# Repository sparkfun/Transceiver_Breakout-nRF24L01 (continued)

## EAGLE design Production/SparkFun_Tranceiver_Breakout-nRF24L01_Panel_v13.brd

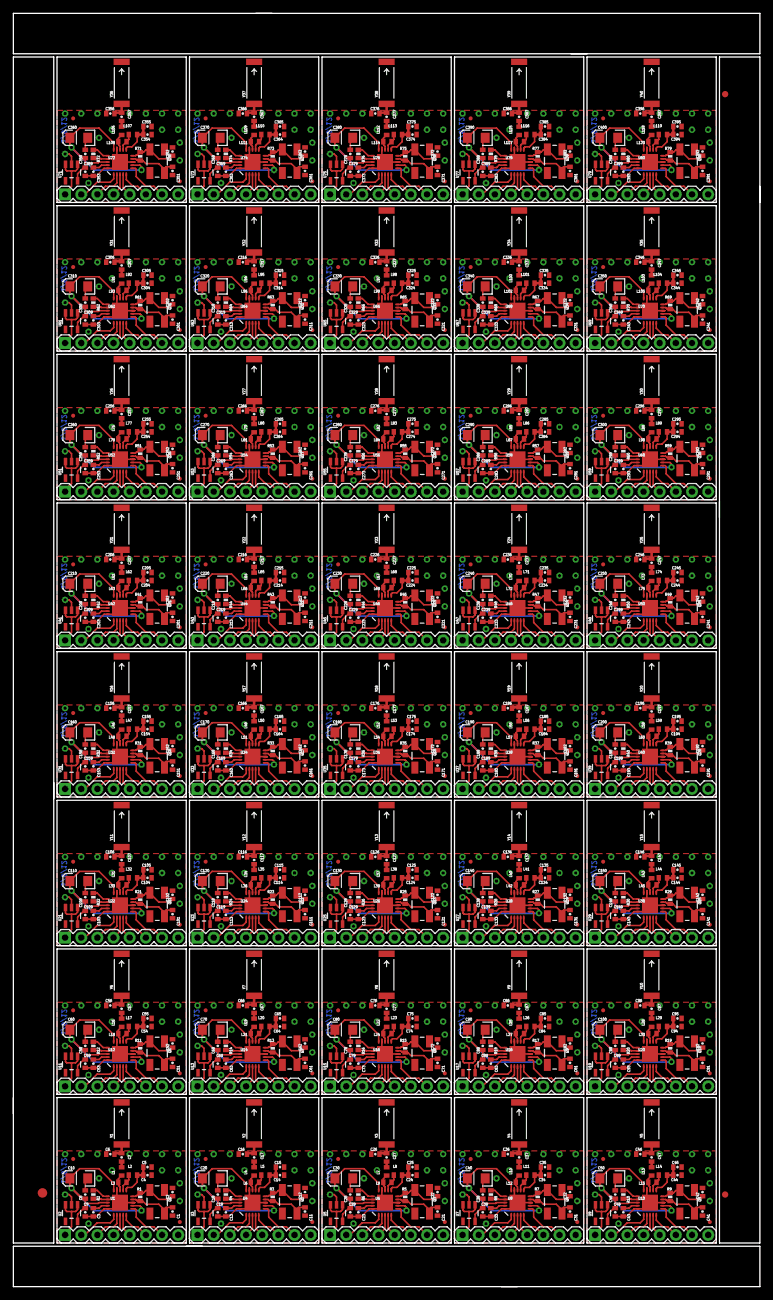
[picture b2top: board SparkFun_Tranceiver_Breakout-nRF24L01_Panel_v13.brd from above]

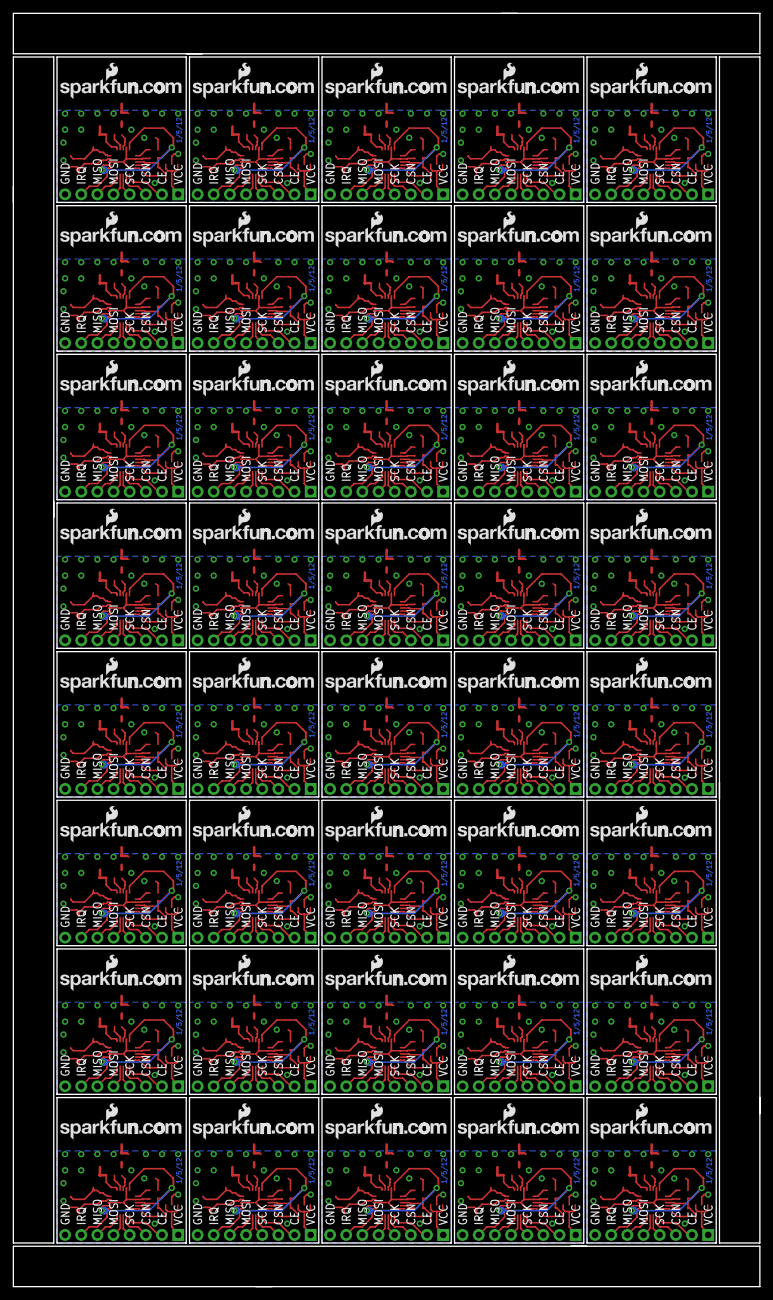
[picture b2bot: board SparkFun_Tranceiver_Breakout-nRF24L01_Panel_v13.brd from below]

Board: 2 copper layers, 117.3 x 200.2 mm, 1043 parts (80 on the bottom side), 720 nets.

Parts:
C1, C2, C11, C12, C21, C22, C31, C32, C41, C42, C51, C52, C61, C62, C71, C72, C81, C82, C91, C92, C101, C102, C111, C112, C121, C122, C131, C132, C141, C142, C151, C152, C161, C162, C171, C172, C181, C182, C191, C192, C201, C202, C211, C212, C221, C222, C231, C232, C241, C242, C251, C252, C261, C262, C271, C272, C281, C282, C291, C292, C301, C302, C311, C312, C321, C322, C331, C332, C341, C342, C351, C352, C361, C362, C371, C372, C381, C382, C391, C392: 22pF; 0402-CAP
C3, C13, C23, C33, C43, C53, C63, C73, C83, C93, C103, C113, C123, C133, C143, C153, C163, C173, C183, C193, C203, C213, C223, C233, C243, C253, C263, C273, C283, C293, C303, C313, C323, C333, C343, C353, C363, C373, C383, C393: 33nF; 0402-CAP
C4, C14, C24, C34, C44, C54, C64, C74, C84, C94, C104, C114, C124, C134, C144, C154, C164, C174, C184, C194, C204, C214, C224, C234, C244, C254, C264, C274, C284, C294, C304, C314, C324, C334, C344, C354, C364, C374, C384, C394: 2.2nF; 0402-CAP
C5, C15, C25, C35, C45, C55, C65, C75, C85, C95, C105, C115, C125, C135, C145, C155, C165, C175, C185, C195, C205, C215, C225, C235, C245, C255, C265, C275, C285, C295, C305, C315, C325, C335, C345, C355, C365, C375, C385, C395: 4.7pF; 0402-CAP
C6, C16, C26, C36, C46, C56, C66, C76, C86, C96, C106, C116, C126, C136, C146, C156, C166, C176, C186, C196, C206, C216, C226, C236, C246, C256, C266, C276, C286, C296, C306, C316, C326, C336, C346, C356, C366, C376, C386, C396: 1.0pF; 0402-CAP
C7, C17, C27, C37, C47, C57, C67, C77, C87, C97, C107, C117, C127, C137, C147, C157, C167, C177, C187, C197, C207, C217, C227, C237, C247, C257, C267, C277, C287, C297, C307, C317, C327, C337, C347, C357, C367, C377, C387, C397: 1.5pF; 0402-CAP
C8, C18, C28, C38, C48, C58, C68, C78, C88, C98, C108, C118, C128, C138, C148, C158, C168, C178, C188, C198, C208, C218, C228, C238, C248, C258, C268, C278, C288, C298, C308, C318, C328, C338, C348, C358, C368, C378, C388, C398: 10nF; 0402-CAP
C9, C19, C29, C39, C49, C59, C69, C79, C89, C99, C109, C119, C129, C139, C149, C159, C169, C179, C189, C199, C209, C219, C229, C239, C249, C259, C269, C279, C289, C299, C309, C319, C329, C339, C349, C359, C369, C379, C389, C399: 1nF; 0402-CAP
C10, C20, C30, C40, C50, C60, C70, C80, C90, C100, C110, C120, C130, C140, C150, C160, C170, C180, C190, C200, C210, C220, C230, C240, C250, C260, C270, C280, C290, C300, C310, C320, C330, C340, C350, C360, C370, C380, C390, C400: 10uF; EIA3216
E$1: FIDUCIAL-1.5X3
E$7, E$8: FIDUCIAL-1X2
JP1, JP4, JP7, JP10, JP13, JP16, JP19, JP22, JP25, JP28, JP31, JP34, JP37, JP40, JP43, JP46, JP49, JP52, JP55, JP58, JP61, JP64, JP67, JP70, JP73, JP76, JP79, JP82, JP85, JP88, JP91, JP94, JP97, JP100, JP103, JP106, JP109, JP112, JP115, JP118: 1X08
JP2, JP3, JP5, JP6, JP8, JP9, JP11, JP12, JP14, JP15, JP17, JP18, JP20, JP21, JP23, JP24, JP26, JP27, JP29, JP30, JP32, JP33, JP35, JP36, JP38, JP39, JP41, JP42, JP44, JP45, JP47, JP48, JP50, JP51, JP53, JP54, JP56, JP57, JP59, JP60, JP62, JP63, JP65, JP66, JP68, JP69, JP71, JP72, JP74, JP75, JP77, JP78, JP80, JP81, JP83, JP84, JP86, JP87, JP89, JP90, JP92, JP93, JP95, JP96, JP98, JP99, JP101, JP102, JP104, JP105, JP107, JP108, JP110, JP111, JP113, JP114, JP116, JP117, JP119, JP120: FIDUCIALUFIDUCIAL; MICRO-FIDUCIAL
L1, L4, L7, L10, L13, L16, L19, L22, L25, L28, L31, L34, L37, L40, L43, L46, L49, L52, L55, L58, L61, L64, L67, L70, L73, L76, L79, L82, L85, L88, L91, L94, L97, L100, L103, L106, L109, L112, L115, L118: 3.9nH; C0402
L2, L5, L8, L11, L14, L17, L20, L23, L26, L29, L32, L35, L38, L41, L44, L47, L50, L53, L56, L59, L62, L65, L68, L71, L74, L77, L80, L83, L86, L89, L92, L95, L98, L101, L104, L107, L110, L113, L116, L119: 2.7nH; C0402
L3, L6, L9, L12, L15, L18, L21, L24, L27, L30, L33, L36, L39, L42, L45, L48, L51, L54, L57, L60, L63, L66, L69, L72, L75, L78, L81, L84, L87, L90, L93, L96, L99, L102, L105, L108, L111, L114, L117, L120: 8.2nH; C0402
Q1, Q2, Q3, Q4, Q5, Q6, Q7, Q8, Q9, Q10, Q11, Q12, Q13, Q14, Q15, Q16, Q17, Q18, Q19, Q20, Q21, Q22, Q23, Q24, Q25, Q26, Q27, Q28, Q29, Q30, Q31, Q32, Q33, Q34, Q35, Q36, Q37, Q38, Q39, Q40: 16MHz; CRYSTAL-SMD-5X3
R1, R3, R5, R7, R9, R11, R13, R15, R17, R19, R21, R23, R25, R27, R29, R31, R33, R35, R37, R39, R41, R43, R45, R47, R49, R51, R53, R55, R57, R59, R61, R63, R65, R67, R69, R71, R73, R75, R77, R79: 1M; 0402-RES
R2, R4, R6, R8, R10, R12, R14, R16, R18, R20, R22, R24, R26, R28, R30, R32, R34, R36, R38, R40, R42, R44, R46, R48, R50, R52, R54, R56, R58, R60, R62, R64, R66, R68, R70, R72, R74, R76, R78, R80: 22K; 0402-RES
TP1, TP2, TP3, TP4, TP5, TP6, TP7, TP8, TP9, TP10, TP11, TP12, TP13, TP14, TP15, TP16, TP17, TP18, TP19, TP20, TP21, TP22, TP23, TP24, TP25, TP26, TP27, TP28, TP29, TP30, TP31, TP32, TP33, TP34, TP35, TP36, TP37, TP38, TP39, TP40: PAD.03X.05
U1, U4, U6, U8, U10, U12, U14, U16, U18, U20, U22, U24, U26, U28, U30, U32, U34, U36, U38, U40, U42, U44, U46, U48, U50, U52, U54, U56, U58, U60, U62, U64, U66, U68, U70, U72, U74, U76, U78, U80: NRF24L01ALT1; QFN20_ALT1
U2, U3, U5, U7, U9, U11, U13, U15, U17, U19, U21, U23, U25, U27, U29, U31, U33, U35, U37, U39, U41, U43, U45, U47, U49, U51, U53, U55, U57, U59, U61, U63, U65, U67, U69, U71, U73, U75, U77, U79: 3.3V; SOT23-5
U$1, U$3, U$4, U$6, U$8, U$9, U$11, U$12, U$14, U$15, U$17, U$18, U$20, U$21, U$23, U$24, U$26, U$27, U$29, U$30, U$32, U$33, U$35, U$36, U$38, U$39, U$41, U$42, U$44, U$45, U$47, U$48, U$50, U$51, U$53, U$54, U$56, U$57, U$59, U$60, U$62, U$63, U$65, U$66, U$68, U$69, U$71, U$72, U$74, U$75, U$77, U$78, U$80, U$81, U$83, U$84, U$86, U$87, U$89, U$90, U$92, U$93, U$95, U$96, U$98, U$99, U$101, U$102, U$104, U$105, U$107, U$108, U$110, U$111, U$113, U$114, U$116, U$117, U$119, U$120: PAD; PAD-0.008
U$2, U$5, U$7, U$10, U$13, U$16, U$19, U$22, U$25, U$28, U$31, U$34, U$37, U$40, U$43, U$46, U$49, U$52, U$55, U$58, U$61, U$64, U$67, U$70, U$73, U$76, U$79, U$82, U$85, U$88, U$91, U$94, U$97, U$100, U$103, U$106, U$109, U$112, U$115, U$118: LOGO-SFENEW; SFE-NEW-WEBLOGO
Y1, Y2, Y3, Y4, Y5, Y6, Y7, Y8, Y9, Y10, Y11, Y12, Y13, Y14, Y15, Y16, Y17, Y18, Y19, Y20, Y21, Y22, Y23, Y24, Y25, Y26, Y27, Y28, Y29, Y30, Y31, Y32, Y33, Y34, Y35, Y36, Y37, Y38, Y39, Y40: ANTENNA2SMD5; ANTENNA-CHIP5

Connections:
ANT: C6.2, C7.2, Y1.FEED
ANT1: C16.2, C17.2, Y2.FEED
ANT2: C26.2, C27.2, Y3.FEED
ANT3: C36.2, C37.2, Y4.FEED
ANT4: C46.2, C47.2, Y5.FEED
ANT5: C56.2, C57.2, Y6.FEED
ANT6: C66.2, C67.2, Y7.FEED
ANT7: C76.2, C77.2, Y8.FEED
ANT8: C86.2, C87.2, Y9.FEED
ANT9: C96.2, C97.2, Y10.FEED
ANT10: C106.2, C107.2, Y11.FEED
ANT11: C116.2, C117.2, Y12.FEED
ANT12: C126.2, C127.2, Y13.FEED
ANT13: C136.2, C137.2, Y14.FEED
ANT14: C146.2, C147.2, Y15.FEED
ANT15: C156.2, C157.2, Y16.FEED
ANT16: C166.2, C167.2, Y17.FEED
ANT17: C176.2, C177.2, Y18.FEED
ANT18: C186.2, C187.2, Y19.FEED
ANT19: C196.2, C197.2, Y20.FEED
ANT20: C206.2, C207.2, Y21.FEED
ANT21: C216.2, C217.2, Y22.FEED
ANT22: C226.2, C227.2, Y23.FEED
ANT23: C236.2, C237.2, Y24.FEED
ANT24: C246.2, C247.2, Y25.FEED
ANT25: C256.2, C257.2, Y26.FEED
ANT26: C266.2, C267.2, Y27.FEED
ANT27: C276.2, C277.2, Y28.FEED
ANT28: C286.2, C287.2, Y29.FEED
ANT29: C296.2, C297.2, Y30.FEED
ANT30: C306.2, C307.2, Y31.FEED
ANT31: C316.2, C317.2, Y32.FEED
ANT32: C326.2, C327.2, Y33.FEED
ANT33: C336.2, C337.2, Y34.FEED
ANT34: C346.2, C347.2, Y35.FEED
ANT35: C356.2, C357.2, Y36.FEED
ANT36: C366.2, C367.2, Y37.FEED
ANT37: C376.2, C377.2, Y38.FEED
ANT38: C386.2, C387.2, Y39.FEED
ANT39: C396.2, C397.2, Y40.FEED
CE: JP1.2, U1.1
CE1: JP4.2, U4.1
CE2: JP7.2, U6.1
CE3: JP10.2, U8.1
CE4: JP13.2, U10.1
CE5: JP16.2, U12.1
CE6: JP19.2, U14.1
CE7: JP22.2, U16.1
CE8: JP25.2, U18.1
CE9: JP28.2, U20.1
CE10: JP31.2, U22.1
CE11: JP34.2, U24.1
CE12: JP37.2, U26.1
CE13: JP40.2, U28.1
CE14: JP43.2, U30.1
CE15: JP46.2, U32.1
CE16: JP49.2, U34.1
CE17: JP52.2, U36.1
CE18: JP55.2, U38.1
CE19: JP58.2, U40.1
CE20: JP61.2, U42.1
CE21: JP64.2, U44.1
CE22: JP67.2, U46.1
CE23: JP70.2, U48.1
CE24: JP73.2, U50.1
CE25: JP76.2, U52.1
CE26: JP79.2, U54.1
CE27: JP82.2, U56.1
CE28: JP85.2, U58.1
CE29: JP88.2, U60.1
CE30: JP91.2, U62.1
CE31: JP94.2, U64.1
CE32: JP97.2, U66.1
CE33: JP100.2, U68.1
CE34: JP103.2, U70.1
CE35: JP106.2, U72.1
CE36: JP109.2, U74.1
CE37: JP112.2, U76.1
CE38: JP115.2, U78.1
CE39: JP118.2, U80.1
CSN: JP1.3, U1.2
CSN1: JP4.3, U4.2
CSN2: JP7.3, U6.2
CSN3: JP10.3, U8.2
CSN4: JP13.3, U10.2
CSN5: JP16.3, U12.2
CSN6: JP19.3, U14.2
CSN7: JP22.3, U16.2
CSN8: JP25.3, U18.2
CSN9: JP28.3, U20.2
CSN10: JP31.3, U22.2
CSN11: JP34.3, U24.2
CSN12: JP37.3, U26.2
CSN13: JP40.3, U28.2
CSN14: JP43.3, U30.2
CSN15: JP46.3, U32.2
CSN16: JP49.3, U34.2
CSN17: JP52.3, U36.2
CSN18: JP55.3, U38.2
CSN19: JP58.3, U40.2
CSN20: JP61.3, U42.2
CSN21: JP64.3, U44.2
CSN22: JP67.3, U46.2
CSN23: JP70.3, U48.2
CSN24: JP73.3, U50.2
CSN25: JP76.3, U52.2
CSN26: JP79.3, U54.2
CSN27: JP82.3, U56.2
CSN28: JP85.3, U58.2
CSN29: JP88.3, U60.2
CSN30: JP91.3, U62.2
CSN31: JP94.3, U64.2
CSN32: JP97.3, U66.2
CSN33: JP100.3, U68.2
CSN34: JP103.3, U70.2
CSN35: JP106.3, U72.2
CSN36: JP109.3, U74.2
CSN37: JP112.3, U76.2
CSN38: JP115.3, U78.2
CSN39: JP118.3, U80.2
GND: C1.2, C2.2, C3.2, C4.2, C5.2, C6.1, C8.1, C9.1, C10.C, JP1.8, R2.2, U1.0, U1.8, U1.14, U1.17, U1.20, U2.2, U$1.P$1, U$4.P$1
GND1: C11.2, C12.2, C13.2, C14.2, C15.2, C16.1, C18.1, C19.1, C20.C, JP4.8, R4.2, U3.2, U4.0, U4.8, U4.14, U4.17, U4.20, U$3.P$1, U$6.P$1
GND2: C21.2, C22.2, C23.2, C24.2, C25.2, C26.1, C28.1, C29.1, C30.C, JP7.8, R6.2, U5.2, U6.0, U6.8, U6.14, U6.17, U6.20, U$8.P$1, U$9.P$1
GND3: C31.2, C32.2, C33.2, C34.2, C35.2, C36.1, C38.1, C39.1, C40.C, JP10.8, R8.2, U7.2, U8.0, U8.8, U8.14, U8.17, U8.20, U$11.P$1, U$12.P$1
GND4: C41.2, C42.2, C43.2, C44.2, C45.2, C46.1, C48.1, C49.1, C50.C, JP13.8, R10.2, U9.2, U10.0, U10.8, U10.14, U10.17, U10.20, U$14.P$1, U$15.P$1
GND5: C51.2, C52.2, C53.2, C54.2, C55.2, C56.1, C58.1, C59.1, C60.C, JP16.8, R12.2, U11.2, U12.0, U12.8, U12.14, U12.17, U12.20, U$17.P$1, U$18.P$1
GND6: C61.2, C62.2, C63.2, C64.2, C65.2, C66.1, C68.1, C69.1, C70.C, JP19.8, R14.2, U13.2, U14.0, U14.8, U14.14, U14.17, U14.20, U$20.P$1, U$21.P$1
GND7: C71.2, C72.2, C73.2, C74.2, C75.2, C76.1, C78.1, C79.1, C80.C, JP22.8, R16.2, U15.2, U16.0, U16.8, U16.14, U16.17, U16.20, U$23.P$1, U$24.P$1
GND8: C81.2, C82.2, C83.2, C84.2, C85.2, C86.1, C88.1, C89.1, C90.C, JP25.8, R18.2, U17.2, U18.0, U18.8, U18.14, U18.17, U18.20, U$26.P$1, U$27.P$1
GND9: C91.2, C92.2, C93.2, C94.2, C95.2, C96.1, C98.1, C99.1, C100.C, JP28.8, R20.2, U19.2, U20.0, U20.8, U20.14, U20.17, U20.20, U$29.P$1, U$30.P$1
GND10: C101.2, C102.2, C103.2, C104.2, C105.2, C106.1, C108.1, C109.1, C110.C, JP31.8, R22.2, U21.2, U22.0, U22.8, U22.14, U22.17, U22.20, U$32.P$1, U$33.P$1
GND11: C111.2, C112.2, C113.2, C114.2, C115.2, C116.1, C118.1, C119.1, C120.C, JP34.8, R24.2, U23.2, U24.0, U24.8, U24.14, U24.17, U24.20, U$35.P$1, U$36.P$1
GND12: C121.2, C122.2, C123.2, C124.2, C125.2, C126.1, C128.1, C129.1, C130.C, JP37.8, R26.2, U25.2, U26.0, U26.8, U26.14, U26.17, U26.20, U$38.P$1, U$39.P$1
GND13: C131.2, C132.2, C133.2, C134.2, C135.2, C136.1, C138.1, C139.1, C140.C, JP40.8, R28.2, U27.2, U28.0, U28.8, U28.14, U28.17, U28.20, U$41.P$1, U$42.P$1
GND14: C141.2, C142.2, C143.2, C144.2, C145.2, C146.1, C148.1, C149.1, C150.C, JP43.8, R30.2, U29.2, U30.0, U30.8, U30.14, U30.17, U30.20, U$44.P$1, U$45.P$1
GND15: C151.2, C152.2, C153.2, C154.2, C155.2, C156.1, C158.1, C159.1, C160.C, JP46.8, R32.2, U31.2, U32.0, U32.8, U32.14, U32.17, U32.20, U$47.P$1, U$48.P$1
GND16: C161.2, C162.2, C163.2, C164.2, C165.2, C166.1, C168.1, C169.1, C170.C, JP49.8, R34.2, U33.2, U34.0, U34.8, U34.14, U34.17, U34.20, U$50.P$1, U$51.P$1
GND17: C171.2, C172.2, C173.2, C174.2, C175.2, C176.1, C178.1, C179.1, C180.C, JP52.8, R36.2, U35.2, U36.0, U36.8, U36.14, U36.17, U36.20, U$53.P$1, U$54.P$1
GND18: C181.2, C182.2, C183.2, C184.2, C185.2, C186.1, C188.1, C189.1, C190.C, JP55.8, R38.2, U37.2, U38.0, U38.8, U38.14, U38.17, U38.20, U$56.P$1, U$57.P$1
GND19: C191.2, C192.2, C193.2, C194.2, C195.2, C196.1, C198.1, C199.1, C200.C, JP58.8, R40.2, U39.2, U40.0, U40.8, U40.14, U40.17, U40.20, U$59.P$1, U$60.P$1
GND20: C201.2, C202.2, C203.2, C204.2, C205.2, C206.1, C208.1, C209.1, C210.C, JP61.8, R42.2, U41.2, U42.0, U42.8, U42.14, U42.17, U42.20, U$62.P$1, U$63.P$1
GND21: C211.2, C212.2, C213.2, C214.2, C215.2, C216.1, C218.1, C219.1, C220.C, JP64.8, R44.2, U43.2, U44.0, U44.8, U44.14, U44.17, U44.20, U$65.P$1, U$66.P$1
GND22: C221.2, C222.2, C223.2, C224.2, C225.2, C226.1, C228.1, C229.1, C230.C, JP67.8, R46.2, U45.2, U46.0, U46.8, U46.14, U46.17, U46.20, U$68.P$1, U$69.P$1
GND23: C231.2, C232.2, C233.2, C234.2, C235.2, C236.1, C238.1, C239.1, C240.C, JP70.8, R48.2, U47.2, U48.0, U48.8, U48.14, U48.17, U48.20, U$71.P$1, U$72.P$1
GND24: C241.2, C242.2, C243.2, C244.2, C245.2, C246.1, C248.1, C249.1, C250.C, JP73.8, R50.2, U49.2, U50.0, U50.8, U50.14, U50.17, U50.20, U$74.P$1, U$75.P$1
GND25: C251.2, C252.2, C253.2, C254.2, C255.2, C256.1, C258.1, C259.1, C260.C, JP76.8, R52.2, U51.2, U52.0, U52.8, U52.14, U52.17, U52.20, U$77.P$1, U$78.P$1
GND26: C261.2, C262.2, C263.2, C264.2, C265.2, C266.1, C268.1, C269.1, C270.C, JP79.8, R54.2, U53.2, U54.0, U54.8, U54.14, U54.17, U54.20, U$80.P$1, U$81.P$1
GND27: C271.2, C272.2, C273.2, C274.2, C275.2, C276.1, C278.1, C279.1, C280.C, JP82.8, R56.2, U55.2, U56.0, U56.8, U56.14, U56.17, U56.20, U$83.P$1, U$84.P$1
GND28: C281.2, C282.2, C283.2, C284.2, C285.2, C286.1, C288.1, C289.1, C290.C, JP85.8, R58.2, U57.2, U58.0, U58.8, U58.14, U58.17, U58.20, U$86.P$1, U$87.P$1
GND29: C291.2, C292.2, C293.2, C294.2, C295.2, C296.1, C298.1, C299.1, C300.C, JP88.8, R60.2, U59.2, U60.0, U60.8, U60.14, U60.17, U60.20, U$89.P$1, U$90.P$1
GND30: C301.2, C302.2, C303.2, C304.2, C305.2, C306.1, C308.1, C309.1, C310.C, JP91.8, R62.2, U61.2, U62.0, U62.8, U62.14, U62.17, U62.20, U$92.P$1, U$93.P$1
GND31: C311.2, C312.2, C313.2, C314.2, C315.2, C316.1, C318.1, C319.1, C320.C, JP94.8, R64.2, U63.2, U64.0, U64.8, U64.14, U64.17, U64.20, U$95.P$1, U$96.P$1
GND32: C321.2, C322.2, C323.2, C324.2, C325.2, C326.1, C328.1, C329.1, C330.C, JP97.8, R66.2, U65.2, U66.0, U66.8, U66.14, U66.17, U66.20, U$98.P$1, U$99.P$1
GND33: C331.2, C332.2, C333.2, C334.2, C335.2, C336.1, C338.1, C339.1, C340.C, JP100.8, R68.2, U67.2, U68.0, U68.8, U68.14, U68.17, U68.20, U$101.P$1, U$102.P$1
GND34: C341.2, C342.2, C343.2, C344.2, C345.2, C346.1, C348.1, C349.1, C350.C, JP103.8, R70.2, U69.2, U70.0, U70.8, U70.14, U70.17, U70.20, U$104.P$1, U$105.P$1
GND35: C351.2, C352.2, C353.2, C354.2, C355.2, C356.1, C358.1, C359.1, C360.C, JP106.8, R72.2, U71.2, U72.0, U72.8, U72.14, U72.17, U72.20, U$107.P$1, U$108.P$1
GND36: C361.2, C362.2, C363.2, C364.2, C365.2, C366.1, C368.1, C369.1, C370.C, JP109.8, R74.2, U73.2, U74.0, U74.8, U74.14, U74.17, U74.20, U$110.P$1, U$111.P$1
GND37: C371.2, C372.2, C373.2, C374.2, C375.2, C376.1, C378.1, C379.1, C380.C, JP112.8, R76.2, U75.2, U76.0, U76.8, U76.14, U76.17, U76.20, U$113.P$1, U$114.P$1
GND38: C381.2, C382.2, C383.2, C384.2, C385.2, C386.1, C388.1, C389.1, C390.C, JP115.8, R78.2, U77.2, U78.0, U78.8, U78.14, U78.17, U78.20, U$116.P$1, U$117.P$1
GND39: C391.2, C392.2, C393.2, C394.2, C395.2, C396.1, C398.1, C399.1, C400.C, JP118.8, R80.2, U79.2, U80.0, U80.8, U80.14, U80.17, U80.20, U$119.P$1, U$120.P$1
IQR: JP1.7, U1.6
IQR1: JP4.7, U4.6
IQR2: JP7.7, U6.6
IQR3: JP10.7, U8.6
IQR4: JP13.7, U10.6
IQR5: JP16.7, U12.6
IQR6: JP19.7, U14.6
IQR7: JP22.7, U16.6
IQR8: JP25.7, U18.6
IQR9: JP28.7, U20.6
IQR10: JP31.7, U22.6
IQR11: JP34.7, U24.6
IQR12: JP37.7, U26.6
IQR13: JP40.7, U28.6
IQR14: JP43.7, U30.6
IQR15: JP46.7, U32.6
IQR16: JP49.7, U34.6
IQR17: JP52.7, U36.6
IQR18: JP55.7, U38.6
IQR19: JP58.7, U40.6
IQR20: JP61.7, U42.6
IQR21: JP64.7, U44.6
IQR22: JP67.7, U46.6
IQR23: JP70.7, U48.6
IQR24: JP73.7, U50.6
IQR25: JP76.7, U52.6
IQR26: JP79.7, U54.6
IQR27: JP82.7, U56.6
IQR28: JP85.7, U58.6
IQR29: JP88.7, U60.6
IQR30: JP91.7, U62.6
IQR31: JP94.7, U64.6
IQR32: JP97.7, U66.6
IQR33: JP100.7, U68.6
IQR34: JP103.7, U70.6
IQR35: JP106.7, U72.6
IQR36: JP109.7, U74.6
IQR37: JP112.7, U76.6
IQR38: JP115.7, U78.6
IQR39: JP118.7, U80.6
MISO: JP1.6, U1.5
MISO1: JP4.6, U4.5
MISO2: JP7.6, U6.5
MISO3: JP10.6, U8.5
MISO4: JP13.6, U10.5
MISO5: JP16.6, U12.5
MISO6: JP19.6, U14.5
MISO7: JP22.6, U16.5
MISO8: JP25.6, U18.5
MISO9: JP28.6, U20.5
MISO10: JP31.6, U22.5
MISO11: JP34.6, U24.5
MISO12: JP37.6, U26.5
MISO13: JP40.6, U28.5
MISO14: JP43.6, U30.5
MISO15: JP46.6, U32.5
MISO16: JP49.6, U34.5
MISO17: JP52.6, U36.5
MISO18: JP55.6, U38.5
MISO19: JP58.6, U40.5
MISO20: JP61.6, U42.5
MISO21: JP64.6, U44.5
MISO22: JP67.6, U46.5
MISO23: JP70.6, U48.5
MISO24: JP73.6, U50.5
MISO25: JP76.6, U52.5
MISO26: JP79.6, U54.5
MISO27: JP82.6, U56.5
MISO28: JP85.6, U58.5
MISO29: JP88.6, U60.5
MISO30: JP91.6, U62.5
MISO31: JP94.6, U64.5
MISO32: JP97.6, U66.5
MISO33: JP100.6, U68.5
MISO34: JP103.6, U70.5
MISO35: JP106.6, U72.5
MISO36: JP109.6, U74.5
MISO37: JP112.6, U76.5
MISO38: JP115.6, U78.5
MISO39: JP118.6, U80.5
MOSI: JP1.5, U1.4
MOSI1: JP4.5, U4.4
MOSI2: JP7.5, U6.4
MOSI3: JP10.5, U8.4
MOSI4: JP13.5, U10.4
MOSI5: JP16.5, U12.4
MOSI6: JP19.5, U14.4
MOSI7: JP22.5, U16.4
MOSI8: JP25.5, U18.4
MOSI9: JP28.5, U20.4
MOSI10: JP31.5, U22.4
MOSI11: JP34.5, U24.4
MOSI12: JP37.5, U26.4
MOSI13: JP40.5, U28.4
MOSI14: JP43.5, U30.4
MOSI15: JP46.5, U32.4
MOSI16: JP49.5, U34.4
MOSI17: JP52.5, U36.4
MOSI18: JP55.5, U38.4
MOSI19: JP58.5, U40.4
MOSI20: JP61.5, U42.4
MOSI21: JP64.5, U44.4
MOSI22: JP67.5, U46.4
MOSI23: JP70.5, U48.4
MOSI24: JP73.5, U50.4
MOSI25: JP76.5, U52.4
MOSI26: JP79.5, U54.4
MOSI27: JP82.5, U56.4
MOSI28: JP85.5, U58.4
MOSI29: JP88.5, U60.4
MOSI30: JP91.5, U62.4
MOSI31: JP94.5, U64.4
MOSI32: JP97.5, U66.4
MOSI33: JP100.5, U68.4
MOSI34: JP103.5, U70.4
MOSI35: JP106.5, U72.4
MOSI36: JP109.5, U74.4
MOSI37: JP112.5, U76.4
MOSI38: JP115.5, U78.4
MOSI39: JP118.5, U80.4
unnamed: C1.1, Q1.1, R1.1, U1.9
unnamed: C2.1, Q1.3, R1.2, U1.10
unnamed: L2.2, L3.1, U1.12
unnamed: R2.1, U1.16
unnamed: C3.1, U1.19
unnamed: L1.1, L3.2, U1.13
unnamed: C4.1, C5.1, L2.1, U1.11
unnamed: C11.1, Q2.1, R3.1, U4.9
unnamed: C7.1, L1.2
unnamed: C12.1, Q2.3, R3.2, U4.10
unnamed: L4.1, L6.2, U4.13
unnamed: C14.1, C15.1, L5.1, U4.11
unnamed: R4.1, U4.16
unnamed: C13.1, U4.19
unnamed: L5.2, L6.1, U4.12
unnamed: C17.1, L4.2
unnamed: C21.1, Q3.1, R5.1, U6.9
unnamed: C22.1, Q3.3, R5.2, U6.10
unnamed: L7.1, L9.2, U6.13
unnamed: C24.1, C25.1, L8.1, U6.11
unnamed: R6.1, U6.16
unnamed: C23.1, U6.19
unnamed: L8.2, L9.1, U6.12
unnamed: C27.1, L7.2
unnamed: C31.1, Q4.1, R7.1, U8.9
unnamed: C32.1, Q4.3, R7.2, U8.10
unnamed: L10.1, L12.2, U8.13
unnamed: C34.1, C35.1, L11.1, U8.11
unnamed: R8.1, U8.16
unnamed: C33.1, U8.19
unnamed: L11.2, L12.1, U8.12
unnamed: C37.1, L10.2
unnamed: C41.1, Q5.1, R9.1, U10.9
unnamed: C42.1, Q5.3, R9.2, U10.10
unnamed: L13.1, L15.2, U10.13
unnamed: C44.1, C45.1, L14.1, U10.11
unnamed: R10.1, U10.16
unnamed: C43.1, U10.19
unnamed: L14.2, L15.1, U10.12
unnamed: C47.1, L13.2
unnamed: C51.1, Q6.1, R11.1, U12.9
unnamed: C52.1, Q6.3, R11.2, U12.10
unnamed: L16.1, L18.2, U12.13
unnamed: C54.1, C55.1, L17.1, U12.11
unnamed: R12.1, U12.16
unnamed: C53.1, U12.19
unnamed: L17.2, L18.1, U12.12
unnamed: C57.1, L16.2
unnamed: C61.1, Q7.1, R13.1, U14.9
unnamed: C62.1, Q7.3, R13.2, U14.10
unnamed: L19.1, L21.2, U14.13
unnamed: C64.1, C65.1, L20.1, U14.11
unnamed: R14.1, U14.16
unnamed: C63.1, U14.19
unnamed: L20.2, L21.1, U14.12
unnamed: C67.1, L19.2
unnamed: C71.1, Q8.1, R15.1, U16.9
unnamed: C72.1, Q8.3, R15.2, U16.10
unnamed: L22.1, L24.2, U16.13
unnamed: C74.1, C75.1, L23.1, U16.11
unnamed: R16.1, U16.16
unnamed: C73.1, U16.19
unnamed: L23.2, L24.1, U16.12
unnamed: C77.1, L22.2
unnamed: C81.1, Q9.1, R17.1, U18.9
unnamed: C82.1, Q9.3, R17.2, U18.10
unnamed: L25.1, L27.2, U18.13
unnamed: C84.1, C85.1, L26.1, U18.11
unnamed: R18.1, U18.16
unnamed: C83.1, U18.19
unnamed: L26.2, L27.1, U18.12
unnamed: C87.1, L25.2
unnamed: C91.1, Q10.1, R19.1, U20.9
unnamed: C92.1, Q10.3, R19.2, U20.10
unnamed: L28.1, L30.2, U20.13
unnamed: C94.1, C95.1, L29.1, U20.11
unnamed: R20.1, U20.16
unnamed: C93.1, U20.19
unnamed: L29.2, L30.1, U20.12
unnamed: C97.1, L28.2
unnamed: C101.1, Q11.1, R21.1, U22.9
unnamed: C102.1, Q11.3, R21.2, U22.10
unnamed: L31.1, L33.2, U22.13
unnamed: C104.1, C105.1, L32.1, U22.11
unnamed: R22.1, U22.16
unnamed: C103.1, U22.19
unnamed: L32.2, L33.1, U22.12
unnamed: C107.1, L31.2
unnamed: C111.1, Q12.1, R23.1, U24.9
unnamed: C112.1, Q12.3, R23.2, U24.10
unnamed: L34.1, L36.2, U24.13
unnamed: C114.1, C115.1, L35.1, U24.11
unnamed: R24.1, U24.16
unnamed: C113.1, U24.19
unnamed: L35.2, L36.1, U24.12
unnamed: C117.1, L34.2
unnamed: C121.1, Q13.1, R25.1, U26.9
unnamed: C122.1, Q13.3, R25.2, U26.10
unnamed: L37.1, L39.2, U26.13
unnamed: C124.1, C125.1, L38.1, U26.11
unnamed: R26.1, U26.16
unnamed: C123.1, U26.19
unnamed: L38.2, L39.1, U26.12
unnamed: C127.1, L37.2
unnamed: C131.1, Q14.1, R27.1, U28.9
unnamed: C132.1, Q14.3, R27.2, U28.10
unnamed: L40.1, L42.2, U28.13
unnamed: C134.1, C135.1, L41.1, U28.11
unnamed: R28.1, U28.16
unnamed: C133.1, U28.19
unnamed: L41.2, L42.1, U28.12
unnamed: C137.1, L40.2
unnamed: C141.1, Q15.1, R29.1, U30.9
unnamed: C142.1, Q15.3, R29.2, U30.10
unnamed: L43.1, L45.2, U30.13
unnamed: C144.1, C145.1, L44.1, U30.11
unnamed: R30.1, U30.16
unnamed: C143.1, U30.19
unnamed: L44.2, L45.1, U30.12
unnamed: C147.1, L43.2
unnamed: C151.1, Q16.1, R31.1, U32.9
unnamed: C152.1, Q16.3, R31.2, U32.10
unnamed: L46.1, L48.2, U32.13
unnamed: C154.1, C155.1, L47.1, U32.11
unnamed: R32.1, U32.16
unnamed: C153.1, U32.19
unnamed: L47.2, L48.1, U32.12
unnamed: C157.1, L46.2
unnamed: C161.1, Q17.1, R33.1, U34.9
unnamed: C162.1, Q17.3, R33.2, U34.10
unnamed: L49.1, L51.2, U34.13
unnamed: C164.1, C165.1, L50.1, U34.11
unnamed: R34.1, U34.16
unnamed: C163.1, U34.19
unnamed: L50.2, L51.1, U34.12
unnamed: C167.1, L49.2
unnamed: C171.1, Q18.1, R35.1, U36.9
unnamed: C172.1, Q18.3, R35.2, U36.10
unnamed: L52.1, L54.2, U36.13
unnamed: C174.1, C175.1, L53.1, U36.11
unnamed: R36.1, U36.16
unnamed: C173.1, U36.19
unnamed: L53.2, L54.1, U36.12
unnamed: C177.1, L52.2
unnamed: C181.1, Q19.1, R37.1, U38.9
unnamed: C182.1, Q19.3, R37.2, U38.10
unnamed: L55.1, L57.2, U38.13
unnamed: C184.1, C185.1, L56.1, U38.11
unnamed: R38.1, U38.16
unnamed: C183.1, U38.19
unnamed: L56.2, L57.1, U38.12
unnamed: C187.1, L55.2
unnamed: C191.1, Q20.1, R39.1, U40.9
unnamed: C192.1, Q20.3, R39.2, U40.10
unnamed: L58.1, L60.2, U40.13
unnamed: C194.1, C195.1, L59.1, U40.11
unnamed: R40.1, U40.16
unnamed: C193.1, U40.19
unnamed: L59.2, L60.1, U40.12
unnamed: C197.1, L58.2
unnamed: C201.1, Q21.1, R41.1, U42.9
unnamed: C202.1, Q21.3, R41.2, U42.10
unnamed: L61.1, L63.2, U42.13
unnamed: C204.1, C205.1, L62.1, U42.11
unnamed: R42.1, U42.16
unnamed: C203.1, U42.19
unnamed: L62.2, L63.1, U42.12
unnamed: C207.1, L61.2
unnamed: C211.1, Q22.1, R43.1, U44.9
unnamed: C212.1, Q22.3, R43.2, U44.10
unnamed: L64.1, L66.2, U44.13
unnamed: C214.1, C215.1, L65.1, U44.11
unnamed: R44.1, U44.16
unnamed: C213.1, U44.19
unnamed: L65.2, L66.1, U44.12
unnamed: C217.1, L64.2
unnamed: C221.1, Q23.1, R45.1, U46.9
unnamed: C222.1, Q23.3, R45.2, U46.10
unnamed: L67.1, L69.2, U46.13
unnamed: C224.1, C225.1, L68.1, U46.11
unnamed: R46.1, U46.16
unnamed: C223.1, U46.19
unnamed: L68.2, L69.1, U46.12
unnamed: C227.1, L67.2
unnamed: C231.1, Q24.1, R47.1, U48.9
unnamed: C232.1, Q24.3, R47.2, U48.10
unnamed: L70.1, L72.2, U48.13
unnamed: C234.1, C235.1, L71.1, U48.11
unnamed: R48.1, U48.16
unnamed: C233.1, U48.19
unnamed: L71.2, L72.1, U48.12
unnamed: C237.1, L70.2
unnamed: C241.1, Q25.1, R49.1, U50.9
unnamed: C242.1, Q25.3, R49.2, U50.10
unnamed: L73.1, L75.2, U50.13
unnamed: C244.1, C245.1, L74.1, U50.11
unnamed: R50.1, U50.16
unnamed: C243.1, U50.19
unnamed: L74.2, L75.1, U50.12
unnamed: C247.1, L73.2
unnamed: C251.1, Q26.1, R51.1, U52.9
unnamed: C252.1, Q26.3, R51.2, U52.10
unnamed: L76.1, L78.2, U52.13
unnamed: C254.1, C255.1, L77.1, U52.11
unnamed: R52.1, U52.16
unnamed: C253.1, U52.19
unnamed: L77.2, L78.1, U52.12
unnamed: C257.1, L76.2
unnamed: C261.1, Q27.1, R53.1, U54.9
unnamed: C262.1, Q27.3, R53.2, U54.10
unnamed: L79.1, L81.2, U54.13
unnamed: C264.1, C265.1, L80.1, U54.11
unnamed: R54.1, U54.16
unnamed: C263.1, U54.19
unnamed: L80.2, L81.1, U54.12
unnamed: C267.1, L79.2
unnamed: C271.1, Q28.1, R55.1, U56.9
unnamed: C272.1, Q28.3, R55.2, U56.10
unnamed: L82.1, L84.2, U56.13
unnamed: C274.1, C275.1, L83.1, U56.11
unnamed: R56.1, U56.16
unnamed: C273.1, U56.19
unnamed: L83.2, L84.1, U56.12
unnamed: C277.1, L82.2
unnamed: C281.1, Q29.1, R57.1, U58.9
unnamed: C282.1, Q29.3, R57.2, U58.10
unnamed: L85.1, L87.2, U58.13
unnamed: C284.1, C285.1, L86.1, U58.11
unnamed: R58.1, U58.16
unnamed: C283.1, U58.19
unnamed: L86.2, L87.1, U58.12
unnamed: C287.1, L85.2
unnamed: C291.1, Q30.1, R59.1, U60.9
unnamed: C292.1, Q30.3, R59.2, U60.10
unnamed: L88.1, L90.2, U60.13
unnamed: C294.1, C295.1, L89.1, U60.11
unnamed: R60.1, U60.16
unnamed: C293.1, U60.19
unnamed: L89.2, L90.1, U60.12
unnamed: C297.1, L88.2
unnamed: C301.1, Q31.1, R61.1, U62.9
unnamed: C302.1, Q31.3, R61.2, U62.10
unnamed: L91.1, L93.2, U62.13
unnamed: C304.1, C305.1, L92.1, U62.11
unnamed: R62.1, U62.16
unnamed: C303.1, U62.19
unnamed: L92.2, L93.1, U62.12
unnamed: C307.1, L91.2
unnamed: C311.1, Q32.1, R63.1, U64.9
unnamed: C312.1, Q32.3, R63.2, U64.10
unnamed: L94.1, L96.2, U64.13
unnamed: C314.1, C315.1, L95.1, U64.11
unnamed: R64.1, U64.16
unnamed: C313.1, U64.19
unnamed: L95.2, L96.1, U64.12
unnamed: C317.1, L94.2
unnamed: C321.1, Q33.1, R65.1, U66.9
unnamed: C322.1, Q33.3, R65.2, U66.10
unnamed: L97.1, L99.2, U66.13
unnamed: C324.1, C325.1, L98.1, U66.11
unnamed: R66.1, U66.16
unnamed: C323.1, U66.19
unnamed: L98.2, L99.1, U66.12
unnamed: C327.1, L97.2
unnamed: C331.1, Q34.1, R67.1, U68.9
unnamed: C332.1, Q34.3, R67.2, U68.10
unnamed: L100.1, L102.2, U68.13
unnamed: C334.1, C335.1, L101.1, U68.11
unnamed: R68.1, U68.16
unnamed: C333.1, U68.19
unnamed: L101.2, L102.1, U68.12
unnamed: C337.1, L100.2
unnamed: C341.1, Q35.1, R69.1, U70.9
unnamed: C342.1, Q35.3, R69.2, U70.10
unnamed: L103.1, L105.2, U70.13
unnamed: C344.1, C345.1, L104.1, U70.11
unnamed: R70.1, U70.16
unnamed: C343.1, U70.19
unnamed: L104.2, L105.1, U70.12
unnamed: C347.1, L103.2
unnamed: C351.1, Q36.1, R71.1, U72.9
unnamed: C352.1, Q36.3, R71.2, U72.10
unnamed: L106.1, L108.2, U72.13
unnamed: C354.1, C355.1, L107.1, U72.11
unnamed: R72.1, U72.16
unnamed: C353.1, U72.19
unnamed: L107.2, L108.1, U72.12
unnamed: C357.1, L106.2
unnamed: C361.1, Q37.1, R73.1, U74.9
unnamed: C362.1, Q37.3, R73.2, U74.10
unnamed: L109.1, L111.2, U74.13
unnamed: C364.1, C365.1, L110.1, U74.11
unnamed: R74.1, U74.16
unnamed: C363.1, U74.19
unnamed: L110.2, L111.1, U74.12
unnamed: C367.1, L109.2
unnamed: C371.1, Q38.1, R75.1, U76.9
unnamed: C372.1, Q38.3, R75.2, U76.10
unnamed: L112.1, L114.2, U76.13
unnamed: C374.1, C375.1, L113.1, U76.11
unnamed: R76.1, U76.16
unnamed: C373.1, U76.19
unnamed: L113.2, L114.1, U76.12
unnamed: C377.1, L112.2
unnamed: C381.1, Q39.1, R77.1, U78.9
unnamed: C382.1, Q39.3, R77.2, U78.10
unnamed: L115.1, L117.2, U78.13
unnamed: C384.1, C385.1, L116.1, U78.11
unnamed: R78.1, U78.16
unnamed: C383.1, U78.19
unnamed: L116.2, L117.1, U78.12
unnamed: C387.1, L115.2
unnamed: C391.1, Q40.1, R79.1, U80.9
unnamed: C392.1, Q40.3, R79.2, U80.10
unnamed: L118.1, L120.2, U80.13
unnamed: C394.1, C395.1, L119.1, U80.11
unnamed: R80.1, U80.16
unnamed: C393.1, U80.19
unnamed: L119.2, L120.1, U80.12
unnamed: C397.1, L118.2
RAW: JP1.1, U2.1, U2.3
RAW1: JP4.1, U3.1, U3.3
RAW2: JP7.1, U5.1, U5.3
RAW3: JP10.1, U7.1, U7.3
RAW4: JP13.1, U9.1, U9.3
RAW5: JP16.1, U11.1, U11.3
RAW6: JP19.1, U13.1, U13.3
RAW7: JP22.1, U15.1, U15.3
RAW8: JP25.1, U17.1, U17.3
RAW9: JP28.1, U19.1, U19.3
RAW10: JP31.1, U21.1, U21.3
RAW11: JP34.1, U23.1, U23.3
RAW12: JP37.1, U25.1, U25.3
RAW13: JP40.1, U27.1, U27.3
RAW14: JP43.1, U29.1, U29.3
RAW15: JP46.1, U31.1, U31.3
RAW16: JP49.1, U33.1, U33.3
RAW17: JP52.1, U35.1, U35.3
RAW18: JP55.1, U37.1, U37.3
RAW19: JP58.1, U39.1, U39.3
RAW20: JP61.1, U41.1, U41.3
RAW21: JP64.1, U43.1, U43.3
RAW22: JP67.1, U45.1, U45.3
RAW23: JP70.1, U47.1, U47.3
RAW24: JP73.1, U49.1, U49.3
RAW25: JP76.1, U51.1, U51.3
RAW26: JP79.1, U53.1, U53.3
RAW27: JP82.1, U55.1, U55.3
RAW28: JP85.1, U57.1, U57.3
RAW29: JP88.1, U59.1, U59.3
RAW30: JP91.1, U61.1, U61.3
RAW31: JP94.1, U63.1, U63.3
RAW32: JP97.1, U65.1, U65.3
RAW33: JP100.1, U67.1, U67.3
RAW34: JP103.1, U69.1, U69.3
RAW35: JP106.1, U71.1, U71.3
RAW36: JP109.1, U73.1, U73.3
RAW37: JP112.1, U75.1, U75.3
RAW38: JP115.1, U77.1, U77.3
RAW39: JP118.1, U79.1, U79.3
SCK: JP1.4, U1.3
SCK1: JP4.4, U4.3
SCK2: JP7.4, U6.3
SCK3: JP10.4, U8.3
SCK4: JP13.4, U10.3
SCK5: JP16.4, U12.3
SCK6: JP19.4, U14.3
SCK7: JP22.4, U16.3
SCK8: JP25.4, U18.3
SCK9: JP28.4, U20.3
SCK10: JP31.4, U22.3
SCK11: JP34.4, U24.3
SCK12: JP37.4, U26.3
SCK13: JP40.4, U28.3
SCK14: JP43.4, U30.3
SCK15: JP46.4, U32.3
SCK16: JP49.4, U34.3
SCK17: JP52.4, U36.3
SCK18: JP55.4, U38.3
SCK19: JP58.4, U40.3
SCK20: JP61.4, U42.3
SCK21: JP64.4, U44.3
SCK22: JP67.4, U46.3
SCK23: JP70.4, U48.3
SCK24: JP73.4, U50.3
SCK25: JP76.4, U52.3
SCK26: JP79.4, U54.3
SCK27: JP82.4, U56.3
SCK28: JP85.4, U58.3
SCK29: JP88.4, U60.3
SCK30: JP91.4, U62.3
SCK31: JP94.4, U64.3
SCK32: JP97.4, U66.3
SCK33: JP100.4, U68.3
SCK34: JP103.4, U70.3
SCK35: JP106.4, U72.3
SCK36: JP109.4, U74.3
SCK37: JP112.4, U76.3
SCK38: JP115.4, U78.3
SCK39: JP118.4, U80.3
VCC: C8.2, C9.2, C10.A, TP1.P$1, U1.7, U1.15, U1.18, U2.5
VCC1: C18.2, C19.2, C20.A, TP2.P$1, U3.5, U4.7, U4.15, U4.18
VCC2: C28.2, C29.2, C30.A, TP3.P$1, U5.5, U6.7, U6.15, U6.18
VCC3: C38.2, C39.2, C40.A, TP4.P$1, U7.5, U8.7, U8.15, U8.18
VCC4: C48.2, C49.2, C50.A, TP5.P$1, U9.5, U10.7, U10.15, U10.18
VCC5: C58.2, C59.2, C60.A, TP6.P$1, U11.5, U12.7, U12.15, U12.18
VCC6: C68.2, C69.2, C70.A, TP7.P$1, U13.5, U14.7, U14.15, U14.18
VCC7: C78.2, C79.2, C80.A, TP8.P$1, U15.5, U16.7, U16.15, U16.18
VCC8: C88.2, C89.2, C90.A, TP9.P$1, U17.5, U18.7, U18.15, U18.18
VCC9: C98.2, C99.2, C100.A, TP10.P$1, U19.5, U20.7, U20.15, U20.18
VCC10: C108.2, C109.2, C110.A, TP11.P$1, U21.5, U22.7, U22.15, U22.18
VCC11: C118.2, C119.2, C120.A, TP12.P$1, U23.5, U24.7, U24.15, U24.18
VCC12: C128.2, C129.2, C130.A, TP13.P$1, U25.5, U26.7, U26.15, U26.18
VCC13: C138.2, C139.2, C140.A, TP14.P$1, U27.5, U28.7, U28.15, U28.18
VCC14: C148.2, C149.2, C150.A, TP15.P$1, U29.5, U30.7, U30.15, U30.18
VCC15: C158.2, C159.2, C160.A, TP16.P$1, U31.5, U32.7, U32.15, U32.18
VCC16: C168.2, C169.2, C170.A, TP17.P$1, U33.5, U34.7, U34.15, U34.18
VCC17: C178.2, C179.2, C180.A, TP18.P$1, U35.5, U36.7, U36.15, U36.18
VCC18: C188.2, C189.2, C190.A, TP19.P$1, U37.5, U38.7, U38.15, U38.18
VCC19: C198.2, C199.2, C200.A, TP20.P$1, U39.5, U40.7, U40.15, U40.18
VCC20: C208.2, C209.2, C210.A, TP21.P$1, U41.5, U42.7, U42.15, U42.18
VCC21: C218.2, C219.2, C220.A, TP22.P$1, U43.5, U44.7, U44.15, U44.18
VCC22: C228.2, C229.2, C230.A, TP23.P$1, U45.5, U46.7, U46.15, U46.18
VCC23: C238.2, C239.2, C240.A, TP24.P$1, U47.5, U48.7, U48.15, U48.18
VCC24: C248.2, C249.2, C250.A, TP25.P$1, U49.5, U50.7, U50.15, U50.18
VCC25: C258.2, C259.2, C260.A, TP26.P$1, U51.5, U52.7, U52.15, U52.18
VCC26: C268.2, C269.2, C270.A, TP27.P$1, U53.5, U54.7, U54.15, U54.18
VCC27: C278.2, C279.2, C280.A, TP28.P$1, U55.5, U56.7, U56.15, U56.18
VCC28: C288.2, C289.2, C290.A, TP29.P$1, U57.5, U58.7, U58.15, U58.18
VCC29: C298.2, C299.2, C300.A, TP30.P$1, U59.5, U60.7, U60.15, U60.18
VCC30: C308.2, C309.2, C310.A, TP31.P$1, U61.5, U62.7, U62.15, U62.18
VCC31: C318.2, C319.2, C320.A, TP32.P$1, U63.5, U64.7, U64.15, U64.18
VCC32: C328.2, C329.2, C330.A, TP33.P$1, U65.5, U66.7, U66.15, U66.18
VCC33: C338.2, C339.2, C340.A, TP34.P$1, U67.5, U68.7, U68.15, U68.18
VCC34: C348.2, C349.2, C350.A, TP35.P$1, U69.5, U70.7, U70.15, U70.18
VCC35: C358.2, C359.2, C360.A, TP36.P$1, U71.5, U72.7, U72.15, U72.18
VCC36: C368.2, C369.2, C370.A, TP37.P$1, U73.5, U74.7, U74.15, U74.18
VCC37: C378.2, C379.2, C380.A, TP38.P$1, U75.5, U76.7, U76.15, U76.18
VCC38: C388.2, C389.2, C390.A, TP39.P$1, U77.5, U78.7, U78.15, U78.18
VCC39: C398.2, C399.2, C400.A, TP40.P$1, U79.5, U80.7, U80.15, U80.18

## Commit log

2015-05-05 Adding hardware and code
2015-05-05 Actually adding hardware files
2015-10-16 created new v13 panel
